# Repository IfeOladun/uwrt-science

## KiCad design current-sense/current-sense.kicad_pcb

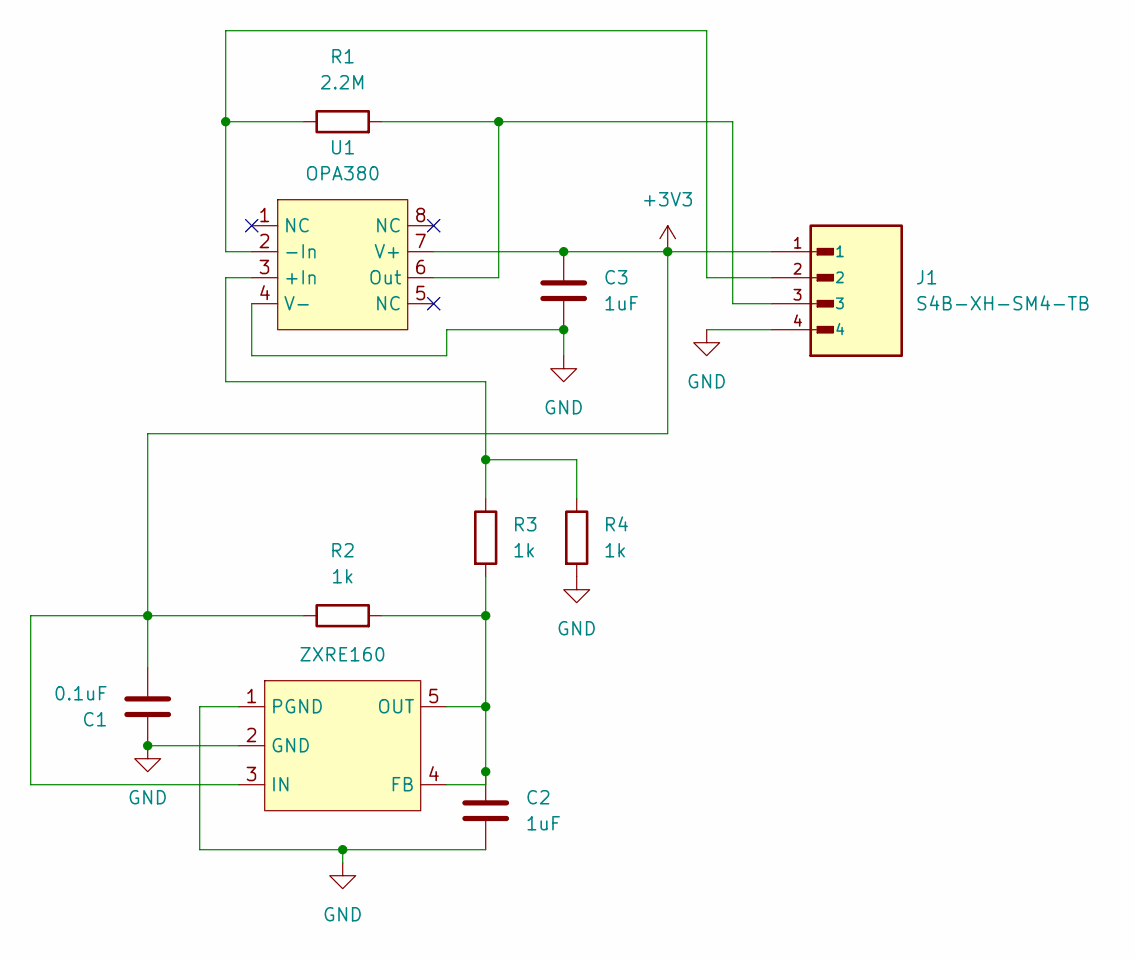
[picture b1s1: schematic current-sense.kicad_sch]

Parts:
C1: 0.1uF; C_0603_1608Metric
C2, C3: 1uF; C_0603_1608Metric
J1: S4B-XH-SM4-TB; JST_S4B-XH-SM4-TB; PARTREV NA
R1: 2.2M; R_0805_2012Metric
R2, R3, R4: 1k; R_0603_1608Metric
U1: OPA380; MSOP-8_3x3mm_P0.65mm
U2: ZXRE160; SOT-353_SC-70-5

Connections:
+3V3: C1.2, C3.1, J1.1, R2.1, U1.7 (V+), U2.3 (IN)
GND: C1.1, C2.2, C3.2, J1.4, R4.2, U1.4 (V-), U2.1 (PGND), U2.2 (GND)
unnamed: R3.1, R4.1, U1.3 (+In)
unnamed: J1.2, R1.1, U1.2 (-In)
unnamed: J1.3, R1.2, U1.6 (Out)
unnamed: C2.1, R2.2, R3.2, U2.4 (FB), U2.5 (OUT)

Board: 2 copper layers, 10 parts (0 on the bottom side), 6 nets, no tracks yet.

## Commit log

2026-03-03 initial
2026-03-04 current sense initial
2026-03-19 steppers
2026-03-19 drilling gui
2026-03-20 spectrometer "gui"
2026-03-22 requirements.txt
2026-04-01 hotfixes
2026-04-17 speed updates
2026-04-23 selection motor cpr fix
